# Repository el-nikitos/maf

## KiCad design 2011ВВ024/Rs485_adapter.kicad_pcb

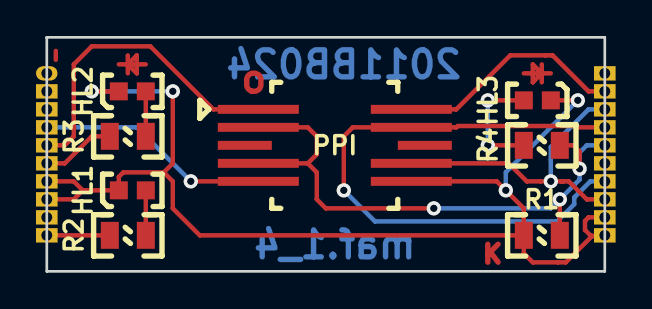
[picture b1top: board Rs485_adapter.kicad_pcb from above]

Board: 2 copper layers, 31.0 x 13.0 mm, 9 parts (0 on the bottom side), 12 nets.

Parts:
A1: 2011ВВ024_adapter; 2011ВВ034_adapter
DD1: Микросхема_5559ИН10; Микросхема_5559ИНхх
HL1, HL2, HL3: Светодиод; Светодиод_SMD_0603
R1, R2, R3, R4: Резистор_0,125Вт; Резистор_SMD_0805_0,125Вт

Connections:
unnamed: A1.1B, A1.2B, A1.7A, A1.8A, DD1.5, HL1.2, HL2.2, HL3.2, R1.2
unnamed: A1.3B, A1.8B, DD1.6
unnamed: A1.4A, DD1.4
unnamed: A1.4B, A1.7B, DD1.7
unnamed: A1.5A, DD1.1
unnamed: A1.6A, R3.2
unnamed: A1.6B, DD1.2, DD1.3, R1.1, R4.1
unnamed: A1.9B, DD1.8
unnamed: A1.10A, R2.2
unnamed: HL1.1, R2.1
unnamed: HL2.1, R3.1
unnamed: HL3.1, R4.2

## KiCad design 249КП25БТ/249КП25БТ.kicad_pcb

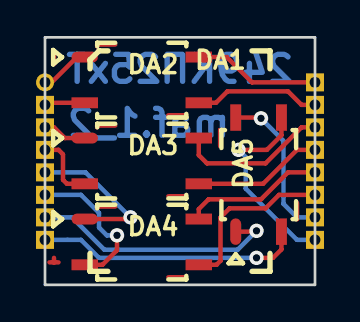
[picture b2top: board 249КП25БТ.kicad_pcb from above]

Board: 2 copper layers, 15.0 x 13.8 mm, 5 parts (0 on the bottom side), 16 nets.

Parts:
DA1: 249КП25АТ; Переходник_МОП-реле_249КП25хТ
DA2, DA3, DA4, DA5: CPC1035NTR(SOP-4); SOP-4

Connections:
/gnd_1: DA1.2, DA2.2
/gnd_2: DA1.4, DA3.2
/gnd_3: DA1.6, DA4.2
/gnd_4: DA1.8, DA5.2
/in_1: DA1.1, DA2.1
/in_2: DA1.3, DA3.1
/in_3: DA1.5, DA4.1
/in_4: DA1.7, DA5.1
/out1_1: DA1.16, DA2.4
/out1_2: DA1.14, DA3.4
/out1_3: DA1.12, DA4.4
/out1_4: DA1.10, DA5.4
/out2_1: DA1.15, DA2.3
/out2_2: DA1.13, DA3.3
/out2_3: DA1.11, DA4.3
/out2_4: DA1.9, DA5.3

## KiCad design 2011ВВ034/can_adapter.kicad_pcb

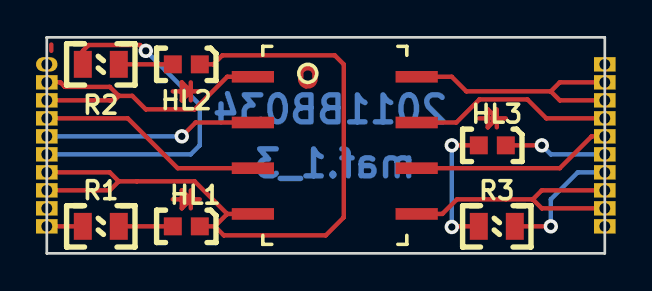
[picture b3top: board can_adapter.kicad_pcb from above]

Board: 2 copper layers, 31.0 x 12.0 mm, 8 parts (0 on the bottom side), 15 nets.

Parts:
A1: 2011ВВ034_adapter
DD1: ISO1050DUB_(CAN)
HL1, HL2, HL3: Светодиод; Светодиод_SMD_0603
R1, R2, R3: Резистор_0,125Вт; Резистор_SMD_0805_0,125Вт

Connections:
unnamed: A1.2A, A1.3A, DD1.1
unnamed: A1.2B, A1.3B, DD1.5
unnamed: A1.4A, DD1.3
unnamed: A1.4B, R3.1
unnamed: A1.5A, DD1.2
unnamed: A1.5B, HL3.2
unnamed: A1.6A, R2.2
unnamed: A1.6B, DD1.6
unnamed: A1.7A, A1.8A, DD1.4, HL1.2, HL2.2
unnamed: A1.7B, DD1.7
unnamed: A1.8B, A1.9B, DD1.8
unnamed: A1.10A, R1.2
unnamed: HL1.1, R1.1
unnamed: HL2.1, R2.1
unnamed: HL3.1, R3.2

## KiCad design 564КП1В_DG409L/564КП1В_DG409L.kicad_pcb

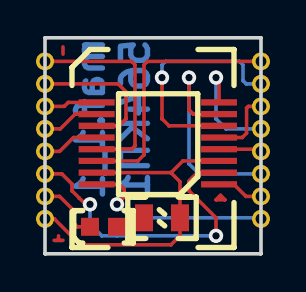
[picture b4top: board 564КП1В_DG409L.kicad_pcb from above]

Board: 2 copper layers, 12.0 x 12.0 mm, 4 parts (0 on the bottom side), 17 nets.

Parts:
DD1: 564П1В; 564КП1В
DD2: DG409LEDQ
HL1: Светодиод; Светодиод_SMD_0603
R1: Резистор_0,125Вт; Резистор_SMD_0805_0,125Вт

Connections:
A: DD1.10, DD2.1
B: DD1.9, DD2.16
C: DD1.6, DD2.2
GND: DD1.8, DD2.3, DD2.15, R1.1
unnamed: DD1.7, HL1.2
unnamed: HL1.1, R1.2
Vcc: DD1.16, DD2.14
X: DD1.13, DD2.8
X0: DD1.12, DD2.4
X1: DD1.14, DD2.5
X2: DD1.15, DD2.6
X3: DD1.11, DD2.7
Y: DD1.3, DD2.9
Y0: DD1.1, DD2.13
Y1: DD1.5, DD2.12
Y2: DD1.2, DD2.11
Y3: DD1.4, DD2.10

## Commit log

2019-03-18 готова 25БТ
2019-03-20 добавлены проекты и файлы производства всех плат
2019-03-21 Резонит плакал
2019-04-19 увеличены зазоры и квадратизированы площадки
